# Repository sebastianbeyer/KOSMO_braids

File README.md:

This is a KOSMO (Look Mum No Computer) version of the Mutable instruments
braids, based on the through-hole version done by
[sound-force.nl](http://sound-force.nl/?page_id=3179).
It has only 12 bits resolution in the output because the chip is easier to work
with and cheaper.

## Changes to original

This project is so far only different to the soundforce version in that I removed the
3.5mm jack sockets and replaced them with molex connectors to get them connected to the
larger 6.3mm jack sockets that KOSMO uses.
And I made the larger KOSMO panel.

This version is still with the old (soundforce-1.1) Version of the soundforce board, without the
termination series resistors on the SPI lines. I had no problems with this, but
I have not changed anything on the BRAIN board, so you can just use the original
gerbers.

## How to build:

Go download the latest gerber files
[here](https://github.com/sebastianbeyer/KOSMO_braids/releases/latest) and use
them to order PCBs. If you use jlcpcb to order, make sure you check "Specify a
location" at "Remove Order Number" for the panel.

For documentation and BOM look at
[sound-force.nl](http://sound-force.nl/?page_id=3179).

## How to program:

BratAttack made an awesome video on how to upload the firmware to the STM32!

## Changelog

### 1.1
Compared to the version in the top picture, I have made the cutout for the
display a little bit smaller and added small "+" and "-" indicators for
modulation and FM.

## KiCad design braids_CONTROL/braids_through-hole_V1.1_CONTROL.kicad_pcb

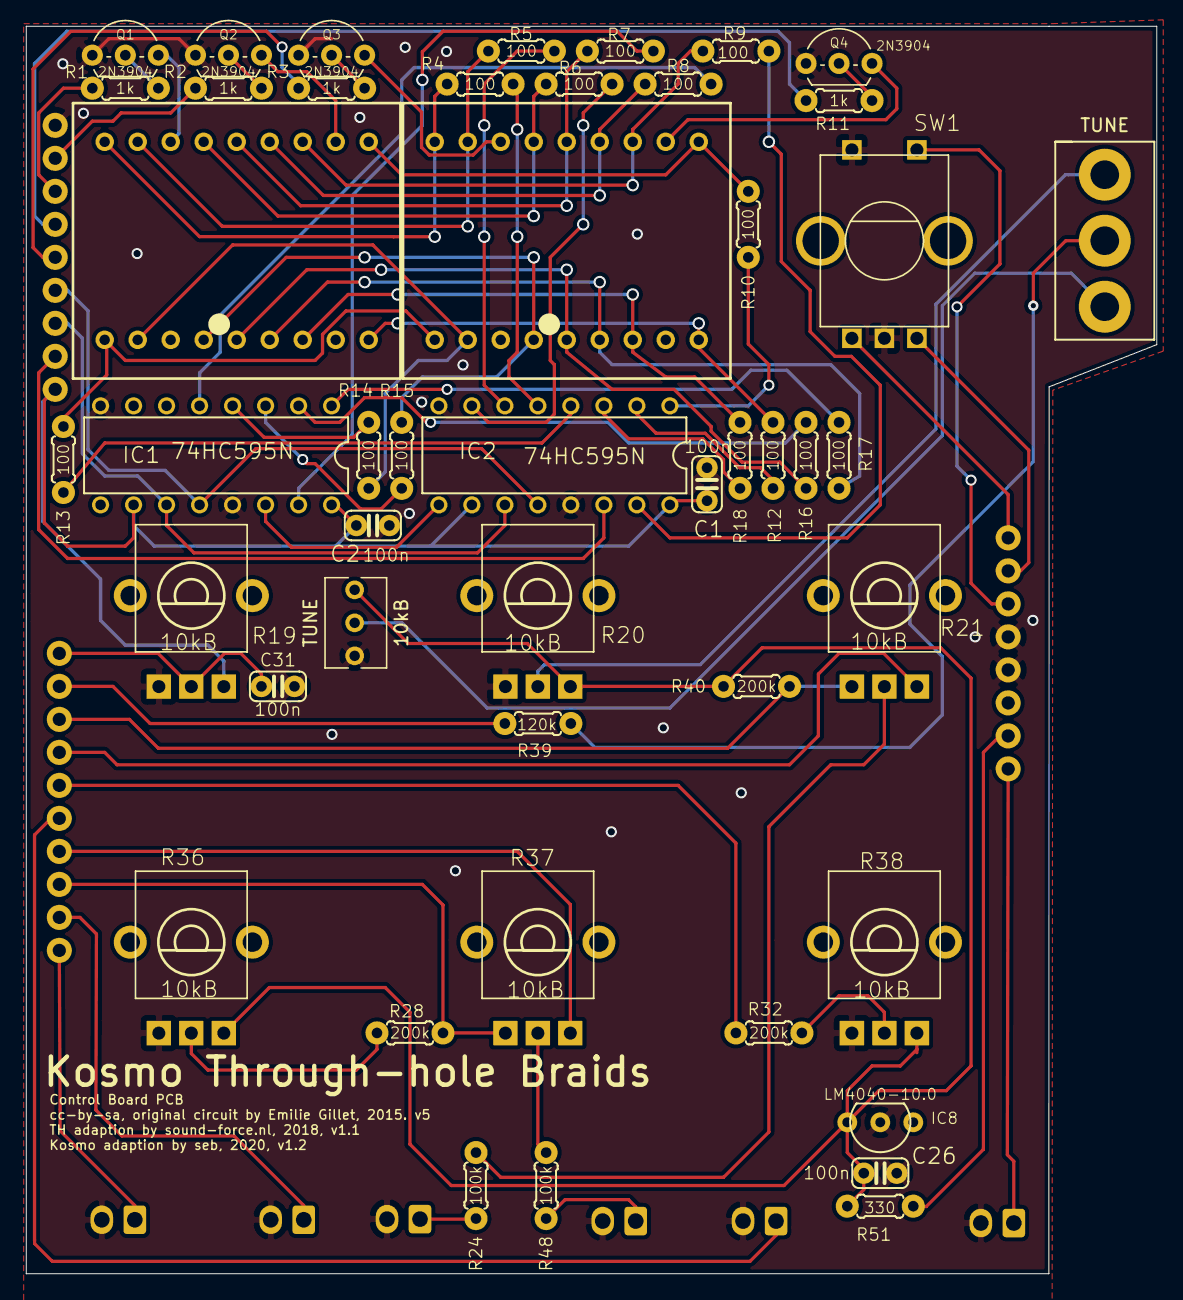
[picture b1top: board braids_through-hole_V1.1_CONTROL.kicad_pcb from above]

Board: 2 copper layers, 87.0 x 96.0 mm, 56 parts (0 on the bottom side), 71 nets.

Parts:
C1, C2, C26, C31: 100n; C025-024X044
COLOR: PJ301_THONKICONN6; Molex_KK-254_AE-6410-02A_1x02_P2.54mm_Vertical
DISP1, DISP2: KINGBRIGHT-PDC54-11; PDC54
DISP_C: 1X09
FM: PJ301_THONKICONN6; Molex_KK-254_AE-6410-02A_1x02_P2.54mm_Vertical
IC1, IC2: 74HC595N; DIL16
IC8: LM4040-10.0; TO127P254X495-3
IN_C: 1X10
OUT: PJ301_THONKICONN6; Molex_KK-254_AE-6410-02A_1x02_P2.54mm_Vertical
PIN_C: 1X08
Q1, Q2, Q3, Q4: 2N3904; TO92-CBE
R1, R2, R3, R11: 1k; 0204_5
R4, R5, R6, R7, R8, R9, R10, R12, R13, R14, R15, R16, R17, R18: 100; 0204_5
R19, R20, R21, R36, R37, R38: 10kB; ALPS_POT_VERTICAL_PS
R24, R48: 100k; 0204_5
R28, R32, R40: 200k; 0204_5
R39: 120k; 0204_5
R51: 330; 0204_5
SW1: EC12E_SW; ALPS_EC12E_SW
TIMBRE: PJ301_THONKICONN6; Molex_KK-254_AE-6410-02A_1x02_P2.54mm_Vertical
TRIG: PJ301_THONKICONN6; Molex_KK-254_AE-6410-02A_1x02_P2.54mm_Vertical
TUNE: SPST SWITCH; SPDT SWITCH
TUNE#2: 10kB; Potentiometer_Bourns_3266Y_Vertical
VOCT: PJ301_THONKICONN6; Molex_KK-254_AE-6410-02A_1x02_P2.54mm_Vertical

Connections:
+3V3_1: C1.1, C2.1, DISP_C.1, IC1.10, IC1.16, IC2.10, IC2.16, R19.P$1
AREF_-10: C26.1, IC8.ANODE, R20.P$1, R36.P$1, R38.P$1, R51.2, TUNE#2.1
COLOR_JACK_1: COLOR.1, IN_C.5
COLOR_POT_1: IN_C.6, R32.2
DISP_CHAR0_1: DISP_C.5, R3.1
DISP_CHAR1_1: DISP_C.6, R11.1
DISP_CHAR2_1: DISP_C.7, R1.1
DISP_CHAR3_1: DISP_C.8, R2.1
DISP_EN_1: DISP_C.4, IC1.12, IC2.12
DISP_SCK_1: DISP_C.3, IC1.11, IC2.11
DISP_SER_1: DISP_C.2, IC2.14
ENC_A_1: PIN_C.2, SW1.B
ENC_B_1: PIN_C.1, SW1.A
ENC_CLICK_1: PIN_C.3, SW1.E
FINE_TUNE_1: C31.1, IN_C.10, R19.P$2
FM_JACK1: FM.1, R24.1
FM_POT_A_1: IN_C.7, R21.P$1
FM_POT_B_1: IN_C.8, R21.P$3, R40.2
GND: C1.2, C2.2, C26.2, C31.2, COLOR.2, DISP_C.9, FM.2, IC1.8, IC1.13, IC2.8, IC2.13, IC8.CATHODE, OUT.2, PIN_C.4, PIN_C.5, Q1.E, Q2.E, Q3.E, Q4.E, R19.P$3, R20.P$3, R36.P$3, R38.P$3, SW1.C, SW1.D, TIMBRE.2, TRIG.2, TUNE#2.3, VOCT.2
unnamed: DISP2.16, Q3.C
unnamed: DISP2.11, Q4.C
unnamed: DISP1.16, Q1.C
unnamed: DISP1.11, Q2.C
unnamed: Q3.B, R3.2
unnamed: Q4.B, R11.2
unnamed: Q1.B, R1.2
unnamed: Q2.B, R2.2
unnamed: DISP1.12, DISP2.12, R9.2
unnamed: DISP1.10, DISP2.10, R10.2
unnamed: DISP1.9, DISP2.9, R12.2
unnamed: DISP1.7, DISP2.7, R18.2
unnamed: DISP1.1, DISP2.1, R13.2
unnamed: DISP1.18, DISP2.18, R4.2
unnamed: DISP1.17, DISP2.17, R5.2
unnamed: DISP1.15, DISP2.15, R6.2
unnamed: DISP1.14, DISP2.14, R7.2
unnamed: DISP1.6, DISP2.6, R17.2
unnamed: DISP1.5, DISP2.5, R16.2
unnamed: DISP1.4, DISP2.4, R15.2
unnamed: DISP1.2, DISP2.2, R14.2
unnamed: DISP1.13, DISP2.13, R8.2
unnamed: IC2.7, R6.1
unnamed: IC1.14, IC2.9
unnamed: IC2.15, R9.1
unnamed: IC2.1, R10.1
unnamed: IC2.2, R12.1
unnamed: IC2.3, R18.1
unnamed: IC2.4, R13.1
unnamed: IC2.5, R4.1
unnamed: IC2.6, R5.1
unnamed: IC1.15, R7.1
unnamed: IC1.1, R17.1
unnamed: IC1.2, R16.1
unnamed: IC1.3, R15.1
unnamed: IC1.4, R14.1
unnamed: IC1.5, R8.1
unnamed: R21.P$2, R24.2
unnamed: R28.1, R36.P$2
unnamed: R37.P$2, R48.2
unnamed: R32.1, R38.P$2
OUT_1: OUT.1, PIN_C.8
TIMBRE_JACK_2: R48.1, TIMBRE.1
TIMBRE_POT_A_1: IN_C.4, R37.P$1
TIMBRE_POT_B_1: IN_C.3, R28.2, R37.P$3
TRIG_JACK_1: IN_C.1, TRIG.1
VEE_1: PIN_C.7, R51.1
VOCT_JACK_1: IN_C.2, VOCT.1
VOCT_POT_1: IN_C.9, R39.2
coarse_knob: R20.P$2, TUNE.1
trim: TUNE.3, TUNE#2.2
tune_sel: R39.1, TUNE.2

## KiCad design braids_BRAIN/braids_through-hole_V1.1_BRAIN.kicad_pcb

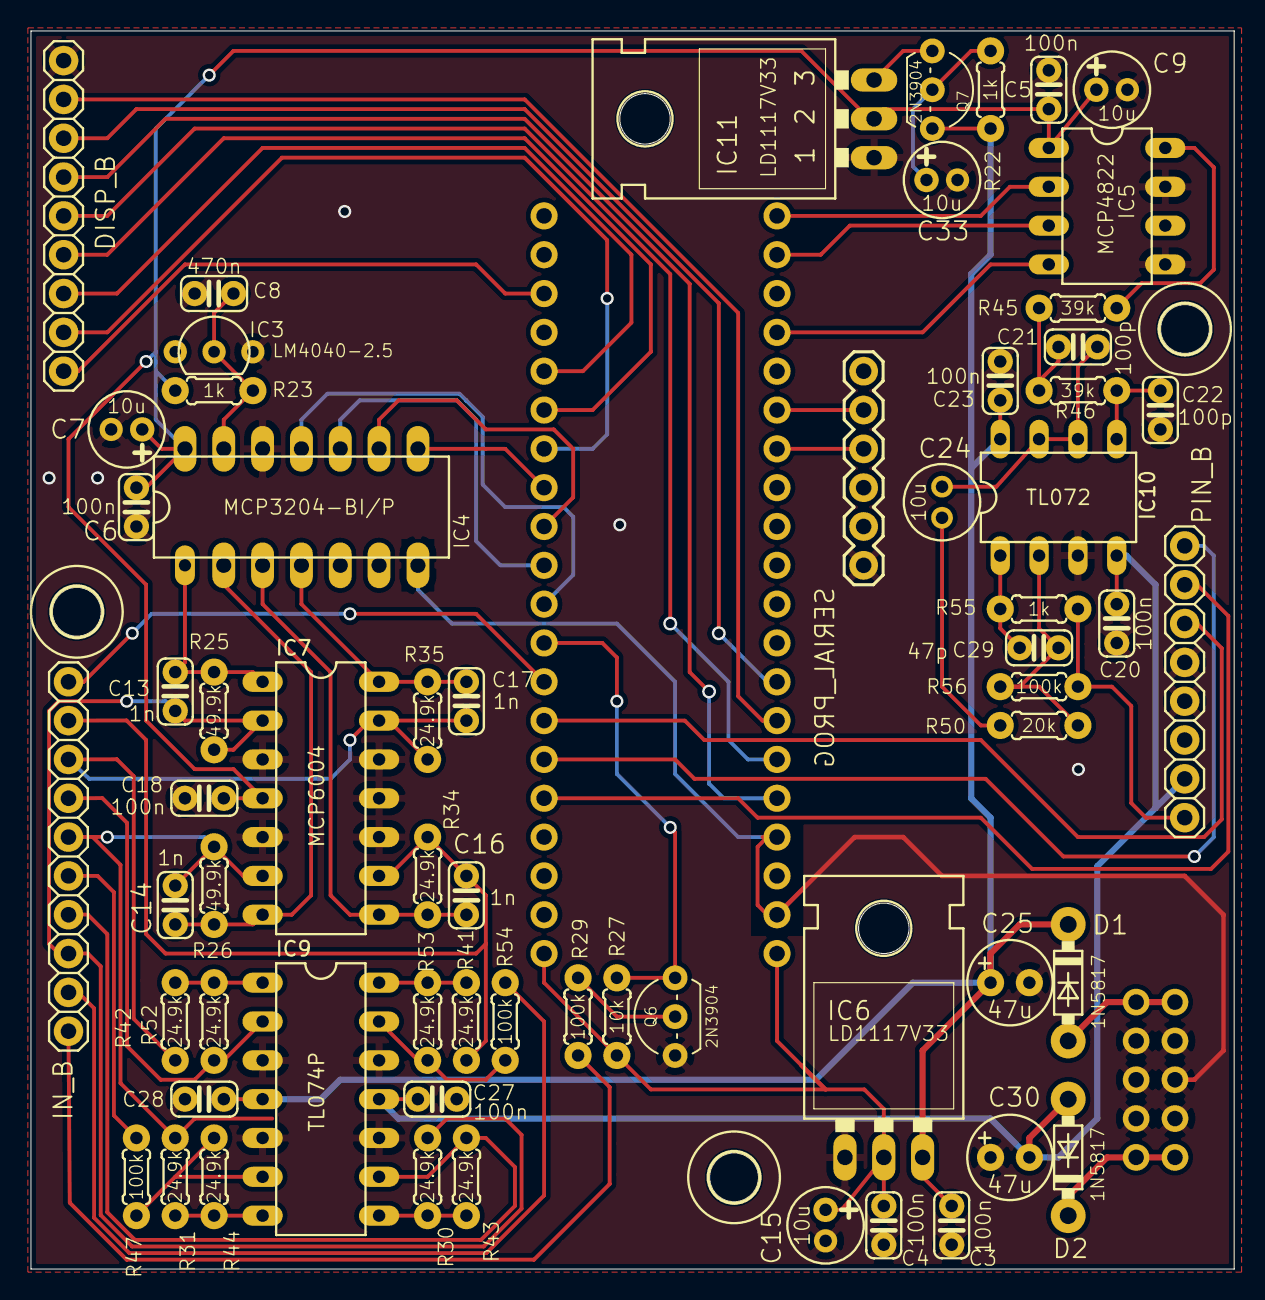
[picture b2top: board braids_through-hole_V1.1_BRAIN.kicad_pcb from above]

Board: 2 copper layers, 78.7 x 81.0 mm, 68 parts (0 on the bottom side), 60 nets.

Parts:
C3, C4, C5, C6, C18, C20, C23, C27, C28: 100n; C025-024X044
C7, C9, C15, C33: 10u; E2-5
C8: 470n; C025-024X044
C13, C14, C16, C17: 1n; C025-024X044
C21, C22: 100p; C025-024X044
C24: 10u; E2-5_NP
C25, C30: 47u; E2,5-6
C29: 47p; C025-024X044
D1, D2: 1N5817; DO41-7.6
DISP_B: 1X09
IC3: LM4040-2.5; TO127P254X495-3
IC4: MCP3204-BI/P; DIP254P762X432-14
IC5: MCP4822
IC6, IC11: LD1117V33; TO220L1
IC7: MCP6004; DIL14
IC9: TL074P; DIL14
IC10: TL072; DIL08
IN_B: 1X10
PIN_B: 1X08
PWR: EURO
Q6, Q7: 2N3904; TO92-CBE
R22, R23, R55: 1k; 0204_5
R25, R26: 49.9k; 0204_5
R27: 10k; 0204_5
R29, R47, R54, R56: 100k; 0204_5
R30, R31, R34, R35, R41, R42, R43, R44, R52, R53: 24.9k; 0204_5
R45, R46: 39k; 0204_5
R50: 20k; 0204_5
SERIAL_PROG: 1X06
U$2, U$3, U$5: 3,2
UC1: STM32F103C8T6

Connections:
+3V3: C4.1, C15.+, IC6.2, R27.2, UC1.3.3V2, UC1.VBAT
+3V3A: C5.1, C6.1, C7.+, C9.+, C18.1, IC4.14, IC5.VCC, IC7.4, IC11.2, R23.1
+3V3_2: DISP_B.1, UC1.3.3V
ADC_MISO: IC4.10, UC1.PA6
ADC_MOSI: IC4.9, UC1.PA7
ADC_SCK: IC4.11, UC1.PA5
ADC_SS: IC4.8, UC1.PB0
AREF: C8.1, IC3.CATHODE, IC4.13, R23.2
AUDIO_OUT: IC5.VOUTA, R45.2
COLOR_JACK_2: IN_B.5, R47.1
COLOR_POT_2: C14.1, IC7.6, IN_B.6, R26.1, R31.2
DAC_MOSI: IC5.SDI, UC1.PB15
DAC_SCK: IC5.SCK, UC1.PB13
DAC_SS: IC5.CS, UC1.PB12
DISP_CHAR0: DISP_B.5, UC1.PB7
DISP_CHAR1: DISP_B.6, UC1.PB8
DISP_CHAR2: DISP_B.7, UC1.PB5
DISP_CHAR3: DISP_B.8, UC1.PB6
DISP_EN: DISP_B.4, UC1.PB10
DISP_SCK: DISP_B.3, UC1.PB11
DISP_SER: DISP_B.2, UC1.PB1
ENC_A: PIN_B.2, UC1.PA0
ENC_B: PIN_B.1, UC1.PA1
ENC_CLICK: PIN_B.3, UC1.PA2
FINE_TUNE_2: IN_B.10, UC1.PA3
FM_CV: C17.2, IC4.4, IC7.14, R35.2
FM_POT_A_2: IC9.2, IN_B.7, R52.1
FM_POT_B_2: C17.1, IC7.13, IN_B.8, R35.1, R42.2
GATE: Q6.C, R27.1, UC1.PA4
GND: C3.2, C4.2, C5.2, C6.2, C7.-, C8.2, C9.-, C15.-, C18.2, C20.1, C22.2, C23.2, C25.-, C27.1, C28.2, C30.+, C33.-, DISP_B.9, IC3.ANODE, IC4.7, IC4.12, IC5.GND, IC5.LDAC, IC6.1, IC7.3, IC7.5, IC7.10, IC7.11, IC7.12, IC9.3, IC9.5, IC9.10, IC9.12, IC10.3, IC11.1, PIN_B.4, PIN_B.5, PWR.3, PWR.4, PWR.5, PWR.6, PWR.7, PWR.8, Q6.E, SERIAL_PROG.1, UC1.GND3, UC1.PB9
unnamed: IC11.3, Q7.E
unnamed: C33.+, Q7.B, R22.1
unnamed: IC9.14, R41.1, R53.2
unnamed: IC9.13, R53.1, R54.2
unnamed: IC9.8, R30.1, R43.2
unnamed: IC9.1, R42.1, R52.2
unnamed: D1.A, PWR.1, PWR.2
unnamed: IC9.7, R31.1, R44.2
unnamed: IC9.6, R44.1, R47.2
unnamed: D2.C, PWR.9, PWR.10
unnamed: Q6.B, R29.2
unnamed: C21.2, C24.+, IC10.6, IC10.7
unnamed: C24.-, R50.2
unnamed: C22.1, IC10.5, R46.1
unnamed: C21.1, R45.1, R46.2
unnamed: C29.2, IC10.1, R55.2
unnamed: C29.1, IC10.2, R50.1, R56.2
OUT: PIN_B.8, R55.1, R56.1
PARAM1_CV: C13.2, IC4.1, IC7.1, R25.2
PARAM2_CV: C14.2, IC4.2, IC7.7, R26.2
PITCH_CV: C16.2, IC4.3, IC7.8, R34.2
RX: SERIAL_PROG.4, UC1.PA10
TIMBRE_POT_A_2: IC9.9, IN_B.4, R43.1
TIMBRE_POT_B_2: C13.1, IC7.2, IN_B.3, R25.1, R30.2
TRIG_JACK_2: IN_B.1, R29.1
TX: SERIAL_PROG.5, UC1.PA9
VCC: C3.1, C23.1, C25.+, C28.1, D1.C, IC6.3, IC9.4, IC10.8, Q7.C, R22.2
VEE: C20.2, C27.2, C30.-, D2.A, IC9.11, IC10.4, PIN_B.7
VOCT_JACK_2: IN_B.2, R54.1
VOCT_POT_2: C16.1, IC7.9, IN_B.9, R34.1, R41.2

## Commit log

2020-08-17 initial with panel stuff
2020-08-17 rename panel dir
2020-08-17 add changes in silkscreen
2020-08-17 add control folder
2020-08-17 add brain board
2020-08-17 add pictures
2020-08-17 smaller images
2020-08-17 fix readme
2020-12-06 add trim switch
2020-12-06 dont know kicad stuff
2022-09-15 update readme with BratAttack video

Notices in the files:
braids_BRAIN/braids_through-hole_V1.1_BRAIN.kicad_pcb:
Brain Board PCB, cc-by-sa,
original circuit by Emilie Gillet, 2015. v5
braids_CONTROL/braids_through-hole_V1.1_CONTROL.kicad_pcb:
cc-by-sa, original circuit by Emilie Gillet, 2015. v5
